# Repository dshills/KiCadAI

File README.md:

# KiCadAI

> **AI proposes. KiCadAI proves—or refuses.**

KiCadAI turns bounded behavioral requirements into deterministic,
evidence-backed native KiCad projects—and stops when it cannot prove a design
inside its reviewed component, model, simulation, and physical-design
envelope.

It is not a prompt-to-schematic wrapper or an unrestricted circuit oracle. The
AI-facing boundary accepts behavior; deterministic code owns architecture and
part selection, calculations, simulation, schematic and PCB generation,
placement, routing, validation, and the final pass-or-refuse decision.

## See The Proof

The featured demo asks for a protected 0.1 A/V programmable current output
across supply, load, startup, temperature, and safe-operating-area corners. Its
input names no component, topology, internal net, value, coordinate, layer, or
route.

```sh
make public-demo
```

On the recorded KiCad 10.0.3 run, KiCadAI derived 43 candidate graphs,
completed and simulated two competing physical architectures, performed 194
candidate simulations and 6,326 corner evaluations, selected real catalog
parts and values, and then generated the same native KiCad project twice.

| Required proof | Recorded result |
|---|---:|
| Behavioral architecture search | 2 complete simulation-passing architectures |
| Placement and routing | 15/15 components placed; 12/12 nets routed |
| Connectivity | 0 unconnected endpoints or DRC unconnected items |
| Writer correctness | 10/10 checks passed |
| KiCad ERC / strict DRC | 0 / 0 violations |
| Normalized KiCad round trip | 0 differences |
| Deterministic physical replay | 2 identical project hashes |

Inspect the [input, native KiCad files, screenshots, commands, compact evidence
receipt, and video storyboard](examples/public-demo/protected-programmable-current-output/README.md).
The receipt binds the requirement, inventory, models, catalog, policy,
architecture ranking, physical output, and verification results with content
hashes. Run `make public-demo-refusal` to verify that an excessive thermal/SOA
request exits unsuccessfully and emits no KiCad project.

This is an ERC/DRC-checked deterministic candidate, **not a fabrication
release**. Human electrical, thermal, mechanical, compliance, and manufacturing
review remains required.

## What Makes It Different

- **Behavior in, proof out.** The open-topology input schema rejects component,
  topology, model, internal-net, value, geometry, route, provider, and repair
  instructions.
- **Search is deterministic and bounded.** Candidate generation, value
  selection, simulation corners, repairs, ranking, and tie-breaking are
  recorded and content-addressed.
- **KiCad is part of the evidence.** KiCadAI writes native `.kicad_sch`,
  `.kicad_pcb`, and `.kicad_pro` files, then uses installed KiCad for ERC,
  strict DRC, and normalized round trips.
- **Failure is a valid result.** Missing evidence, unsafe operating envelopes,
  unsupported behavior, exhausted search, incomplete routing, or validation
  failures stop project promotion instead of being papered over.
- **Claims have boundaries.** Supported, experimental, and unsupported states
  are explicit; experimental output cannot receive a promotion-pass or
  fabrication-ready claim.

The full path is:

```text
behavior → capability gate → topology/value search → trusted simulation
         → native schematic/PCB → placement/routing → KiCad + writer checks
         → identical replay → pass or refusal
```

## Capability At A Glance

| State | What it means today | Evidence |
|---|---|---|
| **Supported** | Reviewed slices of analog, protected current output, low-energy nonlinear/switching, mixed-domain control, MCU, power-tree, sensor, interface, and functional hierarchical four-layer generation can reach deterministic KiCad-backed pass evidence. | [Project status](docs/project-status.md), [mixed-domain held-out audit](specs/multi-stage-out-of-distribution-synthesis/AUDIT.md), [hierarchical four-layer audit](specs/human-quality-hierarchical-multilayer/AUDIT.md) |
| **Experimental** | Broader AI-proposed graphs and capability expansion may generate inspectable artifacts only with explicit opt-in; they cannot be promoted as fabrication-ready. | [Capability gating](docs/capability-gating.md), [AI generation](docs/ai-generation.md) |
| **Unsupported** | Arbitrary circuits and parts, mains/high-energy safety, RF power, unrestricted dense boards, unreviewed models, and automatic fabrication approval remain outside the proven envelope. | [AI readiness](docs/ai-readiness.md), [roadmap](specs/ROADMAP.md) |

The current V18 capability extension adds a version-isolated, catalog-backed
path for low-voltage, high-input-impedance, multi-output analog threshold
requirements. Its public replay case passes deterministic search, coupled value
selection, simulation, physical lowering, and two clean installed-KiCad
promotions without changing the frozen V6–V17 evaluator paths. This remains a
bounded capability, not arbitrary analog synthesis. See the
[V18 specification](specs/closed-loop-open-set-capability-expansion/V18_SPEC_ADDENDUM.md).

V19 tested version-isolated causal-graph invariants, reusable topology
operations, and a deterministic depth-four compositional repair beam. Its
bounded Phase 6 public evaluation completed all 24 cases twice but produced no
passes and did not preserve V18's admitted pass. V19 is therefore permanently
retired and excluded from the v1 supported surface; V18 remains the latest
publicly admitted capability. See the
[V19 retirement audit](specs/closed-loop-open-set-capability-expansion/V19_GENERATION_ZERO_RETIREMENT_AUDIT.md).

The next version-isolated successor adds deterministic analysis, simulation-
model, and solver admission to the production open-topology lane. It derives
analysis needs from behavior, resolves only authenticated bundled or reviewed
overlay model records, records exact model/parameter/source/solver digests,
and refuses before search or numerical evaluation when the combination is not
reproducible. Its frozen V20 public evaluation preserved the V18 pass and
advanced the selected model-availability leaf to a later topology blocker.
It remains an experimental post-v1 capability and does not change the v1
support claim. See the
[specification](specs/generic-analysis-model-solver-admission/SPEC.md) and
[public evidence examples](examples/simulation-admission/README.md).

V21 builds on that admitted V20 boundary with generic causal-topology
completion and bounded repair. It derives structural obligations from behavior,
terminal contracts, and the current graph; applies only canonical generic graph
operations; and preserves exact V20 analysis/model/solver admission before any
new topology work. The September 6 review found unsound structural certificates,
evidence-hash errors, and bound-enforcement defects in its original evaluator.
These are corrected in maintenance revision 1. The original 24-case evaluation
is retained as historical evidence, not validation of the repaired code or
proof of its previously claimed six-case advancement. A separate frozen
maintenance run completed all 24 public cases twice and passed its advancement
and preservation gates: four selected cases across four domains advance to a
later behavioral-evidence blocker, all 16 unselected raw case objects remain
byte-identical to V20, and the V18 pass and safety result are preserved. Outcomes
are 1 pass, 6 unsupported, 1 unsafe, and 16 exhausted; there are no additional
complete circuit passes. V21 remains experimental and does not change the v1
support claim.
See the [review and corrections](docs/project-review-2026-09-06.md) and
[corrected V21 maintenance audit](specs/generic-causal-topology-repair/maintenance-evaluation-1/AUDIT.md).

The subsequent V22 post-topology electrical-repair experiment completed all 24
public cases twice. Compact first-failed-gate diagnostics identified the four
selected candidates' electrical blockers, but bounded generic control-terminal
rebinding produced no additional complete pass. All case outcomes, full replay
hashes, and gate records remain identical to corrected V21; the existing pass
again clears both installed-KiCad promotions. Independent development fixtures
passed, but do not count as corpus improvement. V22 remains experimental and
does not expand v1. See the [root-cause report](specs/post-topology-electrical-blockers/ROOT_CAUSE.md),
[negative evaluation result](specs/post-topology-electrical-blockers/publication-v22/RESULTS.md),
and [timing/evidence-size observations](specs/post-topology-electrical-blockers/publication-v22/PERFORMANCE_OBSERVATIONS.md).

V23 then isolated a generic stale op-amp clamp defect and added a bounded,
version-isolated solver correction. Its separate frozen evaluation completed
all 24 cases twice on September 10: 1 pass, 6 unsupported, 1 unsafe, and 16
exhausted, with no additional complete passes. All case outcomes, full synthesis
replay hashes, and gate records match V22; the existing KiCad-backed pass and
safety outcomes are preserved. The complete retained evidence is authenticated,
but the capability-improvement criterion was not met. V23 remains experimental
and does not expand v1. See the [final results](specs/electrical-repair-followup-v23/publication-v23/RESULTS.md)
and [validation](specs/electrical-repair-followup-v23/publication-v23/LOCAL_VALIDATION.md).

The subsequent practical sensor/controller-board goal remains unachieved.
Its original live baseline produced 0/8 complete boards. The renewed completion
attempt stopped before paid evaluation: six human-authored development probes
failed before electrical synthesis or native generation, with unresolved
requirement/provider qualification and interface-encoding gaps. No new API
requests or complete-board passes were claimed. The full short software suite
passed, but that does not establish practical board readiness. See the
[negative readiness publication](specs/practical-board-completion-v1/README.md)
for retained clauses, evidence, source-bound checks and local-review limits.

The frozen nonlinear/switching corpus provides an additional adversarial
check: five behavior-only positive cases pass, while two unsafe stress cases
and one unsupported dynamic envelope fail closed without a physical project.

The independently frozen mixed-domain corpus composes sensing, decisions,
feedback, nonlinear transfer, switching power, and protection without naming
architectures or parts. Eight feasible requirements reach deterministic
installed-KiCad pass evidence; one contradictory requirement and four unsafe or
unsupported requirements fail closed. See the [completion
audit](specs/multi-stage-out-of-distribution-synthesis/AUDIT.md).

A separately frozen physical-quality corpus proves a bounded next step: four
behavior-only mixed-signal, amplifier, protected-control, and regulated-power
requirements produce functional child sheets and deterministic four-layer
boards. Each passes two clean local installed-KiCad runs with complete routing,
controlled return-path evidence, filled planes, clean ERC/strict DRC, writer
correctness, and zero normalized round-trip differences. This is not a claim
that arbitrary dense boards are supported.

## Run It In Under Ten Minutes

### Maintained source (newer than v1.0.1)

The `schematic`, `capability explore`, `review`, `doctor`, `conformance`, `repro`,
`adapter`, and `family` workflows below were added after the v1.0.1 tag. Build
the maintained source to use them; downloading v1.0.1 does not provide them.
For a small schematic-first workflow that needs no API key, try:

```sh
make build
bin/kicadai --output ./out/divider schematic example divider
bin/kicadai --output ./out/my-session schematic new
```

Open the generated `report.html` for component explanations, calculations and
explicit check statuses. Add `--require-erc` before `schematic` to require native
KiCad validation. See the [guided schematic workflow](docs/schematic-assistant.md).
This produces a schematic candidate, not a board or fabrication approval.

Discover supported workflows with `bin/kicadai capability explore`. For bounded
solver comparisons and compact failure replay, see
[numerical conformance and reproduction](docs/numerical-conformance.md).

For an existing schematic, use `review schematic`; use `doctor` to diagnose
local dependencies. See [project review and local integrations](docs/project-review-and-integration.md)
for catalog self-test kits and the versioned NetForm adapter.

### Published v1.0.1 binary

After [installing and verifying v1.0.1](docs/installation.md), use its supported
direct-file LED example instead. Put global flags **before** the command, and
create the parent output directory first:

```sh
mkdir -p ./out
kicadai --output ./out/led_demo generate-led-demo
# Optional minimal PCB output (not a placed/routed or manufacturing-ready board):
kicadai --output ./out/led_with_pcb --with-pcb generate-led-demo
```

The project files use the output directory's basename unless `--name` is set.
Without `--with-pcb`, only a schematic and project are generated. These offline
examples need neither an API key nor installed KiCad. Native ERC/DRC checks do
require KiCad. These file-writer demos can report ERC/DRC findings; they are not
clean-check acceptance examples (see [check fixtures](examples/checks/README.md)).
v1.0.1 silently ignores trailing flags such as
`generate-led-demo --output DIR`; maintained source rejects them before writing.

Released binaries require no Go installation. KiCad 10.0.3 is the supported v1
reference for installed-KiCad validation and promotion claims. KiCad 9 remains
experimental for those claims. Supported source builds use the exact patched
Go release in [`.go-version`](.go-version) (currently 1.26.10) through Make;
`protoc` is needed only when regenerating vendored protobuf bindings. See the
[v1 support contract](SUPPORT.md) and [v1.0.1 installation guide](docs/installation.md).
v1.0.1 is a security maintenance release; existing v1.0.0 users should replace
their binary, not merely update system Go.

```sh
git clone --branch main https://github.com/dshills/KiCadAI.git
cd KiCadAI
make public-demo
```

The demo detects standard macOS and Linux KiCad installations. If yours is in
a different location, set `KICADAI_KICAD_CLI`, `KICADAI_SYMBOLS_ROOT`, and
`KICADAI_FOOTPRINTS_ROOT` as shown in the
[demo instructions](examples/public-demo/protected-programmable-current-output/README.md#run-it).
The full raw search evidence can approach 1 GB; generated scratch output is
kept in the ignored `examples/.generated/` directory.

For a smaller first look without installed-KiCad proof, build the CLI and use
the direct writers or checked-in educational examples:

```sh
make build
./bin/kicadai --help
./bin/kicadai version
```

Release assets contain four platform binaries, `RELEASE_MANIFEST.json`, and
`SHA256SUMS`. Download the matching binary and verify its checksum before installing it on
your `PATH`. A source checkout can install to `~/.local/bin` with `make
install`; set `INSTALL_DIR` to choose another location. The project publishes a
CLI rather than a supported Go library, so versioned `go install` is not the v1
installation contract.

See [educational circuits](examples/educational/README.md), the
[CLI reference](docs/cli-reference.md), and the preserved
[detailed capability record](docs/capability-record.md).

## AI Generation

Compile an ordinary behavior-first request without allowing the provider to
choose topology, parts, nets, or layout:

```sh
kicadai \
  --file ./behavioral-request.txt \
  --provider openai \
  --ai-profile behavioral-intent-v1 \
  --output ./out/behavioral-request \
  intent compile
```

Only a `ready` result writes
`./out/behavioral-request/.kicadai/behavioral-design-request.json`. A
clarification result writes a hash-bound follow-up template; an unsupported
result writes stable capability-gap evidence and no executable design request.
See [Intent Planning](docs/intent-planning.md#behavioral-intent-compilation) for
the follow-up and project-creation flow.

Run the recorded protected USB-C LED profile with KiCad-backed checks:

```sh
mkdir -p ./out
kicadai --prompt-file examples/ai/usb_c_led_indicator_protected/prompt.txt \
  --provider recorded \
  --provider-record examples/ai/usb_c_led_indicator_protected/recorded-response.json \
  --output ./out/ai_usb_c_led_protected --overwrite \
  --kicad-cli /path/to/kicad-cli \
  --require-kicad-roundtrip --strict-diffs \
  design create
```

For a live request, load `OPENAI_API_KEY` from the shell or a secret manager and
replace the recorded-provider flags with `--provider openai`. Provider output is
strict-decoded and remains untrusted until deterministic and KiCad-backed gates
pass.

Agents that already have a valid `generic-circuit-v1` graph can avoid a provider:

```sh
kicadai capability generation --json
kicadai --request ./graph.json circuit preflight
kicadai --symbols-root /path/to/kicad-symbols \
  --footprints-root /path/to/kicad-footprints \
  circuit create --request ./graph.json --output ./out/project --overwrite
```

For rejected generic graphs, run `circuit repair-plan` first. It selects an
executable patch only when one safe correction is fully derived; otherwise it
stops for review. See the [CLI reference](docs/cli-reference.md#generic-circuit-repair-plan)
for the strict patch contract and evidence boundary.

See [AI Generation](docs/ai-generation.md) for bounded and generic modes, live
commands, evidence files, failure behavior, and current limits. AI agents
should also follow the [KiCadAI Agent Skill](docs/kicadai-agent-skill.md).

## Reproduce Promotion Evidence

From an unmodified checkout, run:

```sh
make promotion-bundle
make held-out-promotion-bundle
```

The command builds the repository CLIs, resolves the version and stock
libraries locked by `toolchain/kicad-promotion.lock.json`, bootstraps the
checksum-pinned distribution only when needed, executes every required scenario
twice, verifies all promotion gates and deterministic comparisons, and writes
one content-addressed bundle below
`.tmp/clean-checkout-promotion/bundles/`. No manually configured KiCad or
library paths are required. The output directory must not already exist.
The held-out target uses the same locked toolchain and verifier with the
versioned five-scenario matrix for the two newly supported families, writing
below `.tmp/held-out-capability-promotion/`.

Use `bundle-path.txt` to locate the bundle. Its included files and semantic
promotion claims can be verified offline:

```sh
.tmp/clean-checkout-promotion/bin/kicadai-promotion verify \
  --bundle "$(cat .tmp/clean-checkout-promotion/bundle-path.txt)"
```

This is release-validation evidence for the supported corpus, not a claim that
arbitrary designs or fabrication outputs are automatically qualified.

## Schematic IR

The schematic design/layout IR is a strict JSON handoff for circuit intent,
layout intent, and repair policy. It is not free-form natural language or KiCad
S-expression syntax.

```sh
kicadai --request examples/schematic-ir/led_indicator.json schematic-ir validate
kicadai --request examples/schematic-ir/led_indicator.json schematic-ir normalize
kicadai --request examples/schematic-ir/led_indicator.json \
  --output ./out/ir_led --overwrite schematic-ir write
```

See [Intent Planning And AI Workflow](docs/intent-planning.md) and the
[CLI Reference](docs/cli-reference.md).

## Documentation

Start with the [documentation index](docs/README.md).

| Topic | Reference |
|---|---|
| Featured end-to-end proof | [Protected Programmable Current Output](examples/public-demo/protected-programmable-current-output/README.md) |
| Current capabilities and limits | [Project Status](docs/project-status.md) |
| v1 platforms, compatibility, and support boundary | [Support Contract](SUPPORT.md) |
| Release history and safety reporting | [Changelog](CHANGELOG.md), [Security](SECURITY.md) |
| Detailed implementation record | [Capability Record](docs/capability-record.md) |
| Educational generated schematics | [Educational Examples](examples/educational/README.md) |
| Commands and live IPC | [CLI Reference](docs/cli-reference.md) |
| Natural-language provider workflow | [AI Generation](docs/ai-generation.md) |
| Behavioral compilation, structured intent, and planning | [Intent Planning](docs/intent-planning.md) |
| Circuit blocks | [Circuit Blocks](docs/circuit-blocks.md) |
| Components, symbols, and footprints | [Libraries And Components](docs/libraries-and-components.md) |
| Placement and routing | [Placement And Routing](docs/layout-routing.md) |
| Validation, writer checks, and round-trip | [Validation And Analysis](docs/validation-and-analysis.md) |
| Clean-checkout release evidence | [Validation And Analysis](docs/validation-and-analysis.md#reproducible-promotion-bundles) |
| Fabrication evidence | [Fabrication](docs/fabrication.md) |
| Direct KiCad file writers | [KiCad File Writers](docs/kicad-file-writers.md) |
| Tests, packages, and troubleshooting | [Development Reference](docs/development.md) |
| Specifications, evidence, and audits | [Specs Index](specs/INDEX.md) |
| Priorities toward broader autonomy | [Roadmap](specs/ROADMAP.md) |

## Development

```sh
make test
make lint
make build
make release-reproducibility
```

See [Development Reference](docs/development.md) for focused tests, coverage,
protobuf maintenance, package boundaries, and troubleshooting.

## License

KiCadAI is licensed under the [MIT License](LICENSE). Vendored KiCad API
materials under `third_party/kicad/` retain their upstream licenses.

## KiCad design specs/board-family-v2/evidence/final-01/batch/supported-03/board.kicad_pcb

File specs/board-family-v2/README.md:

# Two deterministic board families — live acceptance failed

**September 14, 2026:** the complete frozen evaluation achieved 8/14 application outcomes and 4/14 full raw-response passes. An unsupported continuous-heater request generated a board despite the SHT31 heater-off qualification. Do not use the natural-language workflow unattended or treat native validation as proof that every requested behavior is supported. See [results](RESULTS.md) and [release-blocking review](REVIEW.md). PR #14 remains draft; no further live requests are authorized.

The shared `kicadai-board-family` command supports the existing BMP280 pressure board and the SHT31 temperature/humidity board. Both use the fixed ESP32 controller/support design. This is bounded family selection and deterministic construction, not arbitrary schematic or board synthesis.

Offline inspection:

```sh
go run ./cmd/kicadai-board-family --list-families
```

Offline generation plus native/export validation:

```sh
go run ./cmd/kicadai-board-family \
  --config specs/board-family-v2/configurations/sht31-standard.json \
  --output /tmp/kicadai-sht31-new-project \
  --kicad-cli /Applications/KiCad/KiCad.app/Contents/MacOS/kicad-cli
```

The output directory must be new. Use `sht31-fast.json` for the second SHT31 profile; the three existing `examples/board-family-v1/*/configuration.json` configurations remain supported. KiCad 10.0.3 is required for this qualification version. Native subprocesses do not inherit provider keys.

Each successful command produces native project and library files, configuration/electrical reports, BOM JSON/CSV, schematic/PCB previews and `validation.json`. The `manufacturing` directory adds nine Gerber layers with job metadata, PTH/NPTH drills and SVG maps, a drill report, all-component placement CSV and a source-bound file-hash manifest. Any failed native gate withholds exports; any failed export gate makes the command fail. Existing manufacturing directories are never silently overwritten.

Placement coordinates use the absolute board origin, millimeters and negative native-board Y. The CSV includes through-hole headers and requires assembler confirmation of orientations. KiCad's Gerber-job dimensions include outline stroke width; the nominal centerline is 120x80 mm. Native timestamps are retained in raw exports. These files do not constitute an order, machine setup, fabrication signoff or proof of working hardware.

The two-family natural-language contract is implemented and can be inspected without a call:

```sh
go run ./cmd/kicadai-board-family \
  --export-live-contract /tmp/kicadai-two-family-contract.json
```

The separately approved 14-request/USD 1.00 final batch is complete and its request slots are exhausted. The old 41-request budget and ledger also remain exhausted and unchanged. Neither ledger may be reset or reused as new authority. See the [actual approval](evaluation/APPROVAL-01.json) and [recorded results](RESULTS.md); the low estimated cost does not authorize additional attempts.

See [work log](WORK.md), [SHT31 restrictions](SHT31.md), [consolidated electrical/assembly-data review](ELECTRICAL_ASSEMBLY_REVIEW.md), [published examples](../../examples/board-family-v2/README.md) and [current deterministic replay](evidence/deterministic-replay-02.json). All five explicit configurations passed two fresh rounds of native/export validation after the SHT31 mask/paste correction. The five offline example bundles contain 256 byte-identical copied files; 201 deliverables pass repeat-generation comparison. Earlier manufacturing-review records remain historical checkpoints, not qualification of the revised footprint. Final live evidence is complete but acceptance failed; physical assembly/bench qualification is a separate milestone.

The schema uses closed objects and family-specific nested alternatives following [OpenAI Structured Outputs](https://developers.openai.com/api/docs/guides/structured-outputs). The existing pinned GPT-4.1-mini model, transport and retry/accounting policy were not migrated. Export options were checked against the installed executable and [KiCad 10 CLI documentation](https://docs.kicad.org/10.0/en/cli/cli.html).

The separate v2 budget controls and fixed-batch runner are now offline-qualified. [Runtime 01](evaluation/runtime-01.json) binds the budget-enabled binary, selected Go/assembly/embedded dependencies, tests and generated artifacts. Five fresh explicit-configuration builds still match all 201 previously reviewed deliverables; the frozen model payload is unchanged. This is not live language acceptance. Read [execution safeguards and review](evaluation/RUNNER-REVIEW-01.md) before running the offline preflight:

```sh
node specs/board-family-v2/evaluation/run-language.mjs --check
```

The [budget policy](evaluation/budget-01.json) is **not spending authorization**. The separate approval and final ledger now exist and are bound to the retained evaluation. Frozen preparation documents correctly retain their pre-approval status as history. Do not invoke `--live` or `--resume` again: every planned case has been attempted. Use the offline post-run audit in [RESULTS.md](RESULTS.md) to verify the preserved publication.

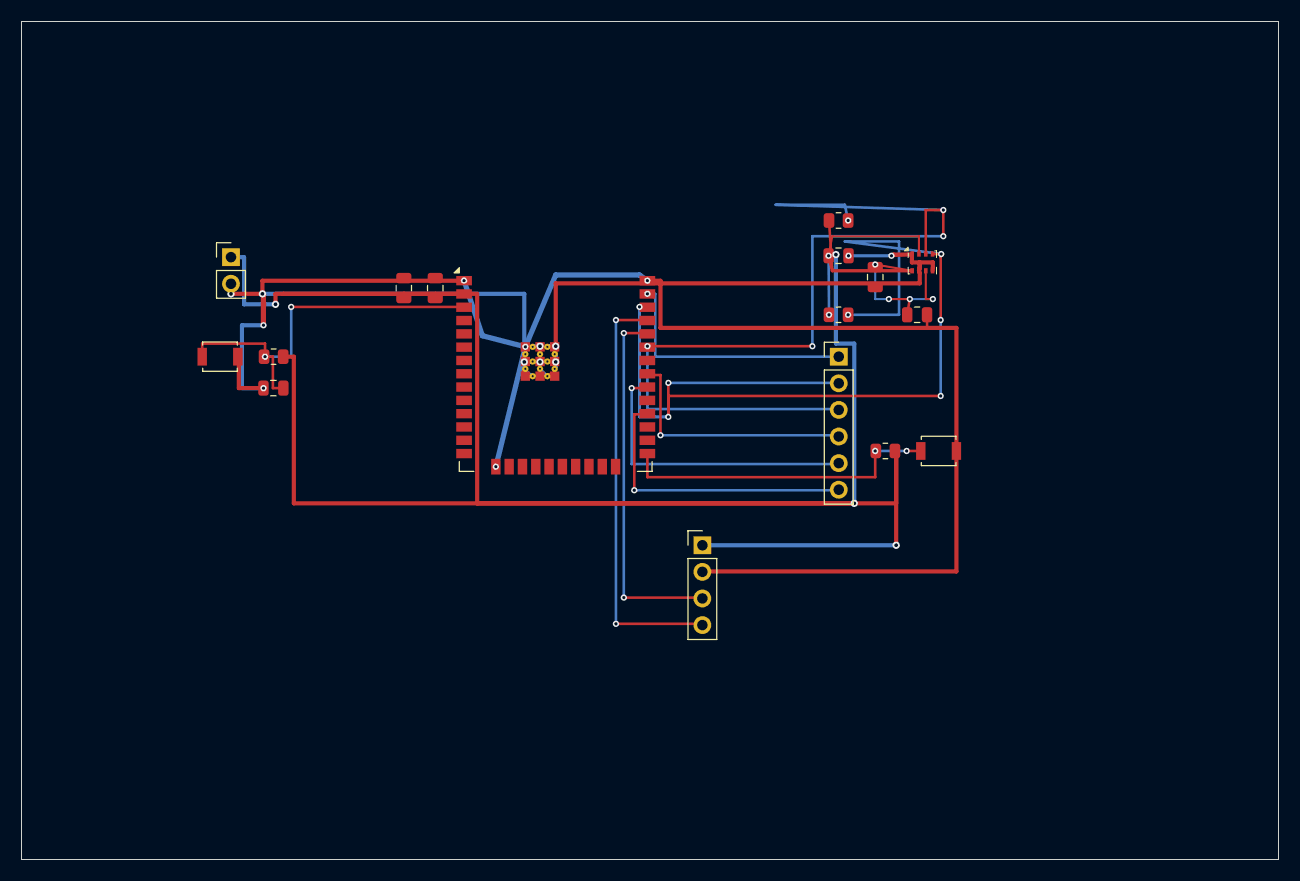
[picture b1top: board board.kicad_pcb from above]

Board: 2 copper layers, 120.0 x 80.0 mm, 17 parts (0 on the bottom side), 12 nets.

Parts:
C1, C4, C5, C6: 100nF; C_0805_2012Metric
C2: 10uF; C_0805_2012Metric
C3: 1uF; C_0805_2012Metric
J1: 3V3 INPUT; PinHeader_1x02_P2.54mm_Vertical
J2: 3V3 UART; PinHeader_1x04_P2.54mm_Vertical
J3: GPIO I2C SPI; PinHeader_1x06_P2.54mm_Vertical
R1, R2, R3, R4: 10k; R_0805_2012Metric
SW1: RESET; SW_SPST_B3U-1000P
SW2: BOOT; SW_SPST_B3U-1000P
U1: ESP32-WROOM-32E-N4; ESP32-WROOM-32E
U2: BMP280 0x76; Bosch_LGA-8_2x2.5mm_P0.65mm_ClockwisePinNumbering

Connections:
/GND: C1.2, C2.2, C3.2, C4.2, C5.2, C6.2, J1.2, J2.2, SW1.2, SW2.2, U1.1, U1.15, U1.38, U1.39, U2.1, U2.5, U2.7
/GPIO: J3.6, U1.28
/MISO: J3.4, U1.31
/MOSI: J3.1, U1.37
/SCK: J3.5, U1.30
/SCL: J3.2, R4.2, U1.36, U2.4
/SDA: J3.3, R3.2, U1.33, U2.3
/VCC: C1.1, C2.1, C4.1, C5.1, C6.1, J1.1, J2.1, R1.1, R2.1, R3.1, R4.1, U1.2, U2.2, U2.6, U2.8
/controller_boot: R2.2, SW2.1, U1.25
/controller_enable: C3.1, R1.2, SW1.1, U1.3
/controller_uart_rx: J2.3, U1.34
/controller_uart_tx: J2.4, U1.35

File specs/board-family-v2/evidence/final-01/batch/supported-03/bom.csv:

Reference,Value,Manufacturer,MPN,Footprint
C1,100nF,Murata,GRM21BR71H104KA01L,Capacitor_SMD:C_0805_2012Metric
C2,10uF,Murata,GRM21BR61A106KE19L,Capacitor_SMD:C_0805_2012Metric
C3,1uF,Murata,GCM21BR71H105KA03L,Capacitor_SMD:C_0805_2012Metric
C4,100nF,Murata,GRM21BR71H104KA01L,Capacitor_SMD:C_0805_2012Metric
C5,100nF,Murata,GRM21BR71H104KA01L,Capacitor_SMD:C_0805_2012Metric
C6,100nF,Murata,GRM21BR71H104KA01L,Capacitor_SMD:C_0805_2012Metric
J1,3V3 INPUT,Samtec,TSW-102-07-L-S,Connector_PinHeader_2.54mm:PinHeader_1x02_P2.54mm_Vertical
J2,3V3 UART,Samtec,TSW-104-07-L-S,Connector_PinHeader_2.54mm:PinHeader_1x04_P2.54mm_Vertical
J3,GPIO I2C SPI,Samtec,TSW-106-07-L-S,Connector_PinHeader_2.54mm:PinHeader_1x06_P2.54mm_Vertical
R1,10k,Yageo,RC0805FR-0710KL,Resistor_SMD:R_0805_2012Metric
R2,10k,Yageo,RC0805FR-0710KL,Resistor_SMD:R_0805_2012Metric
R3,10k,Yageo,RC0805FR-0710KL,Resistor_SMD:R_0805_2012Metric
R4,10k,Yageo,RC0805FR-0710KL,Resistor_SMD:R_0805_2012Metric
SW1,RESET,Omron,B3U-1000P,Button_Switch_SMD:SW_SPST_B3U-1000P
SW2,BOOT,Omron,B3U-1000P,Button_Switch_SMD:SW_SPST_B3U-1000P
U1,ESP32-WROOM-32E-N4,Espressif,ESP32-WROOM-32E-N4,RF_Module:ESP32-WROOM-32E
U2,BMP280 0x76,Bosch Sensortec,BMP280,Package_LGA:Bosch_LGA-8_2x2.5mm_P0.65mm_ClockwisePinNumbering

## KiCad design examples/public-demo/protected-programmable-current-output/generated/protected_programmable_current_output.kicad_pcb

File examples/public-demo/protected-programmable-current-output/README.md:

# Protected Programmable Current Output

This is KiCadAI's featured public demonstration: a behavior-only request for a
0.1 A/V programmable current output, evaluated across supply, load, startup,
temperature, and safe-operating-area constraints.

The input contains no components, topology, internal nets, values, placement,
or routes. KiCadAI derives and ranks physical architectures, selects catalog
parts and values, generates native KiCad files, routes the board, invokes
KiCad ERC and strict DRC, checks connectivity and writer round trips, and then
repeats the complete physical run to prove deterministic output.

## Run It

From the repository root, with KiCad 9 or newer installed:

```sh
make public-demo
```

The script detects the standard macOS or Linux KiCad installation. Override
discovery when necessary:

```sh
KICADAI_KICAD_CLI=/path/to/kicad-cli \
KICADAI_SYMBOLS_ROOT=/path/to/kicad-symbols \
KICADAI_FOOTPRINTS_ROOT=/path/to/kicad-footprints \
  make public-demo
```

The run writes ignored scratch output under
`examples/.generated/public-demo/protected-programmable-current-output/`.
Expect roughly one minute on a current laptop and allow about 1 GB for the
complete topology-search evidence. Open the `run-1/*.kicad_pro` file in KiCad.

To exercise the fail-closed path with an excessive 48 V to 5 V, 4 A,
85 degrees C requirement:

```sh
make public-demo-refusal
```

The underlying `kicadai` command is expected to exit unsuccessfully. The
wrapper verifies that no KiCad project was emitted and then exits successfully
when the refusal contract holds. The public command reports the bounded
search/capability refusal; the frozen nonlinear-switching promotion corpus
additionally checks that this case contains thermal, SOA, or rated-envelope
rejection evidence.

## What Was Proven

| Gate | Result |
|---|---:|
| Candidate architectures | 2 complete, both simulation-passing |
| Search work | 43 graphs, 194 simulations, 6,326 corner evaluations |
| Selected physical circuit | 12 synthesized primitives plus 3 interfaces |
| Placement and routing | 15/15 placed, 12/12 nets routed |
| Connectivity | 0 unconnected endpoints or DRC unconnected items |
| Writer correctness | 10/10 checks passed |
| KiCad 10.0.3 ERC | 0 violations |
| KiCad 10.0.3 strict DRC | 0 violations |
| Round trip | 0 normalized differences |
| Determinism | 2 runs, identical project hash |

The compact, checked-in [evidence receipt](evidence/receipt.json) records the
content hashes, competing architecture ranks, selected parts, and individual
verification gates. Reproduction retains the full raw synthesis and promotion
reports locally in `.kicadai/`; those reports are hundreds of megabytes and
are intentionally not duplicated in Git.

## Inspect Without Running

- [Behavior-only requirement](requirement.json)
- [Compact evidence receipt](evidence/receipt.json)
- [Fail-closed evidence receipt](evidence/refusal-receipt.json)
- [Native KiCad project](generated/protected_programmable_current_output.kicad_pro)
- [Native schematic](generated/protected_programmable_current_output.kicad_sch)
- [Native PCB](generated/protected_programmable_current_output.kicad_pcb)
- [Generated transaction provenance](generated/provenance/transaction.json)
- [60-second video storyboard](VIDEO_STORYBOARD.md)
- [Evidence interpretation and boundaries](EVIDENCE.md)

The generated schematic and PCB are evidence-bearing machine output, not a
hand-redrawn marketing illustration. The board image above is a KiCad render
of the checked-in PCB.

## Boundary

This result is an ERC/DRC-checked deterministic candidate, not a fabrication
release. Human electrical, thermal, mechanical, compliance, and manufacturing
review is still required before building hardware.

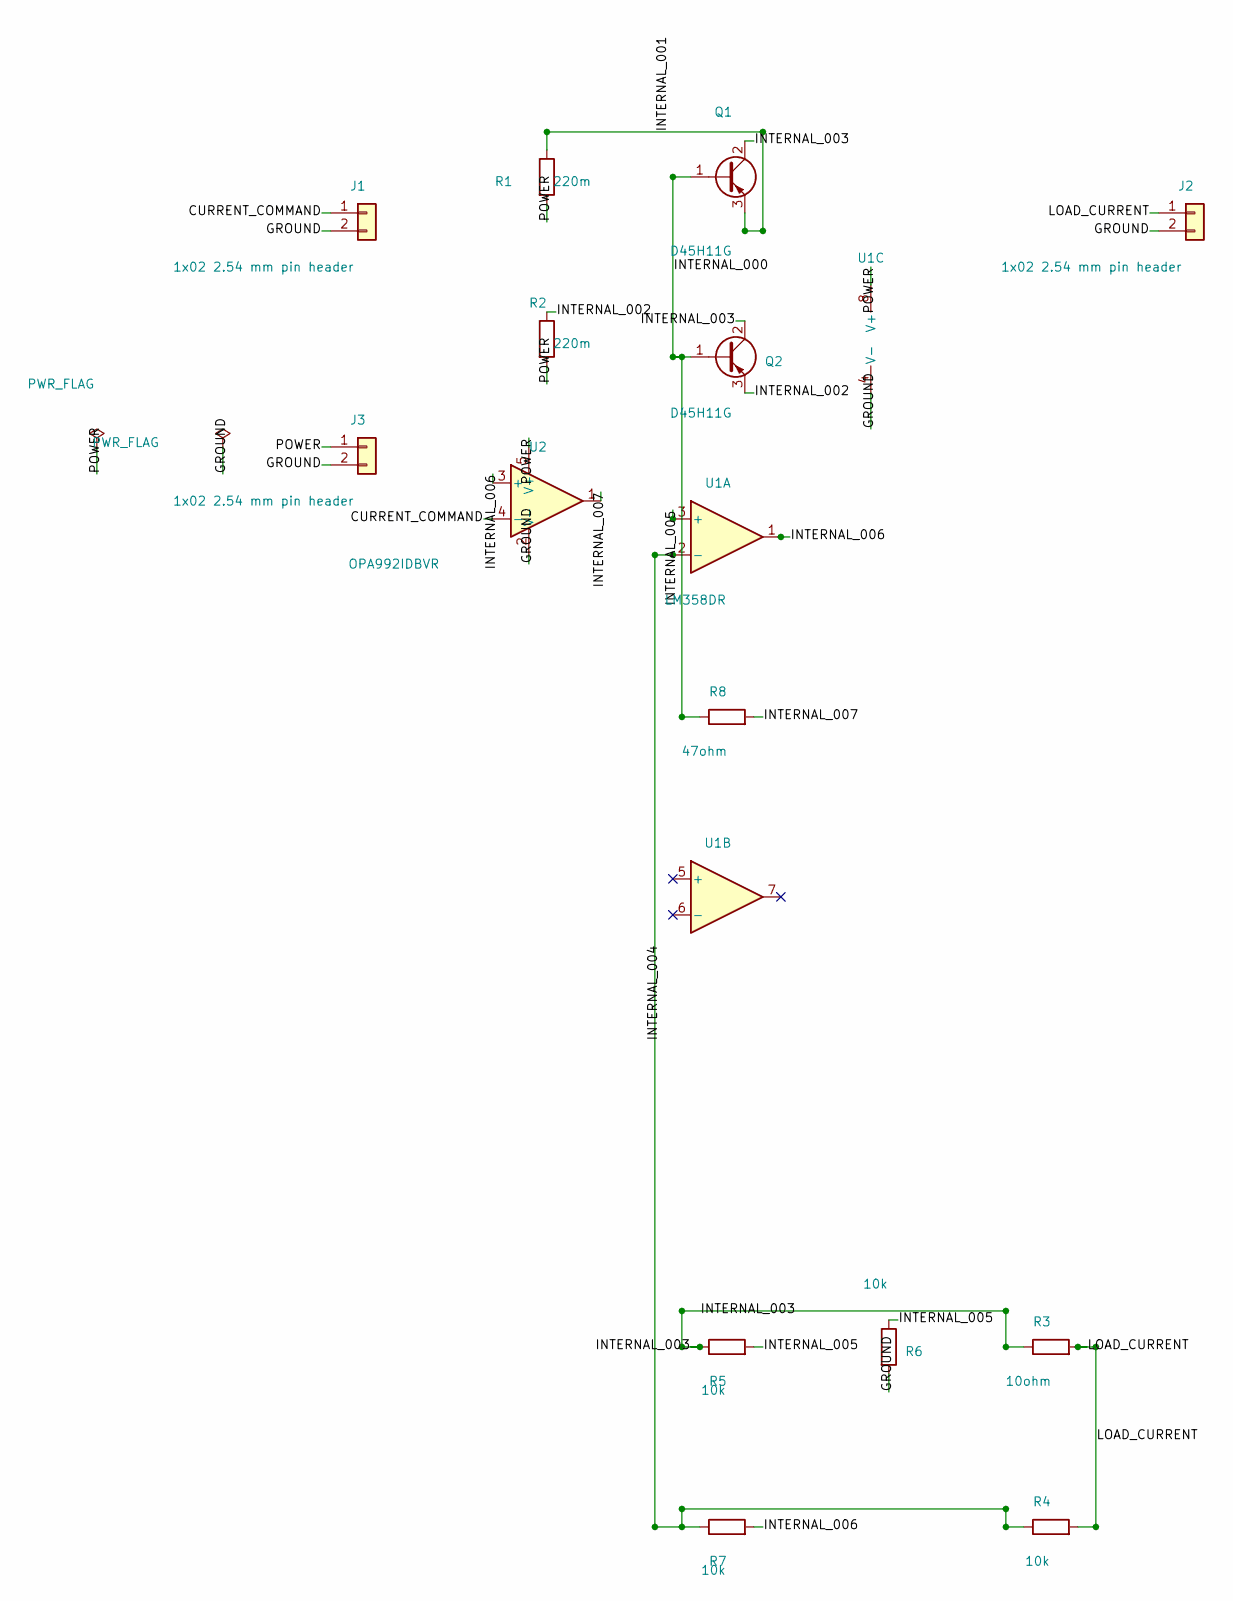
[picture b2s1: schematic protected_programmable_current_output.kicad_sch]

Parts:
J1, J2, J3: 1x02 2.54 mm pin header; PinHeader_1x02_P2.54mm_Vertical
Q1, Q2: D45H11G; TO-220-3_Vertical; MPN D45H11G
R1, R2: 220m; R_Axial_DIN0414_L11.9mm_D4.5mm_P20.32mm_Horizontal; MPN AC03000002207JAC00
R3: 10ohm; R_Axial_DIN0614_L14.3mm_D5.7mm_P25.40mm_Horizontal; MPN CPF310R000BE14
R4, R5, R6, R7: 10k; R_0805_2012Metric; MPN TNPW080510K0BEEA
R8: 47ohm; R_0805_2012Metric; MPN CRCW080547R0FKEA
U1: LM358DR; SOIC-8_3.9x4.9mm_P1.27mm; MPN LM358DR
U2: OPA992IDBVR; SOT-23-5; MPN OPA992IDBVR

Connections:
CURRENT_COMMAND: J1.1, U2.4 (-)
GROUND: J1.2, J2.2, J3.2, R6.2, U1.4 (V-), U2.2 (V-)
INTERNAL_000: Q1.1 (B), Q2.1 (B), R8.1
INTERNAL_001: Q1.3 (E), R1.1
INTERNAL_002: Q2.3 (E), R2.1
INTERNAL_003: Q1.2 (C), Q2.2 (C), R3.1, R5.1
INTERNAL_004: R4.1, R7.1, U1.2 (-)
INTERNAL_005: R5.2, R6.1, U1.3 (+)
INTERNAL_006: R7.2, U1.1, U2.3 (+)
INTERNAL_007: R8.2, U2.1
LOAD_CURRENT: J2.1, R3.2, R4.2
POWER: J3.1, R1.2, R2.2, U1.8 (V+), U2.5 (V+)

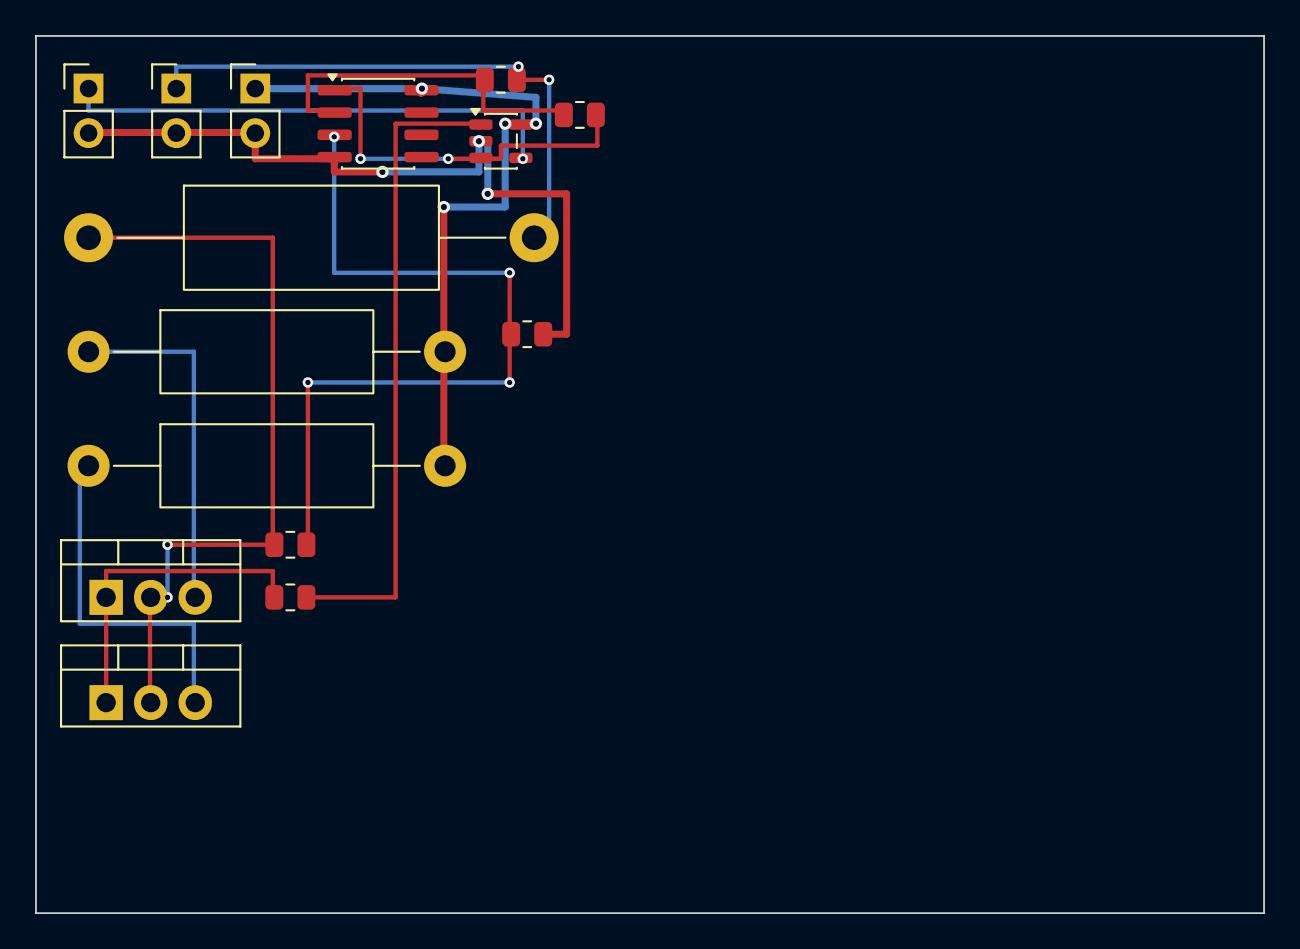
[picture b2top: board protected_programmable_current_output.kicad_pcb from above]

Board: 2 copper layers, 70.0 x 50.0 mm, 15 parts (0 on the bottom side), 12 nets.
